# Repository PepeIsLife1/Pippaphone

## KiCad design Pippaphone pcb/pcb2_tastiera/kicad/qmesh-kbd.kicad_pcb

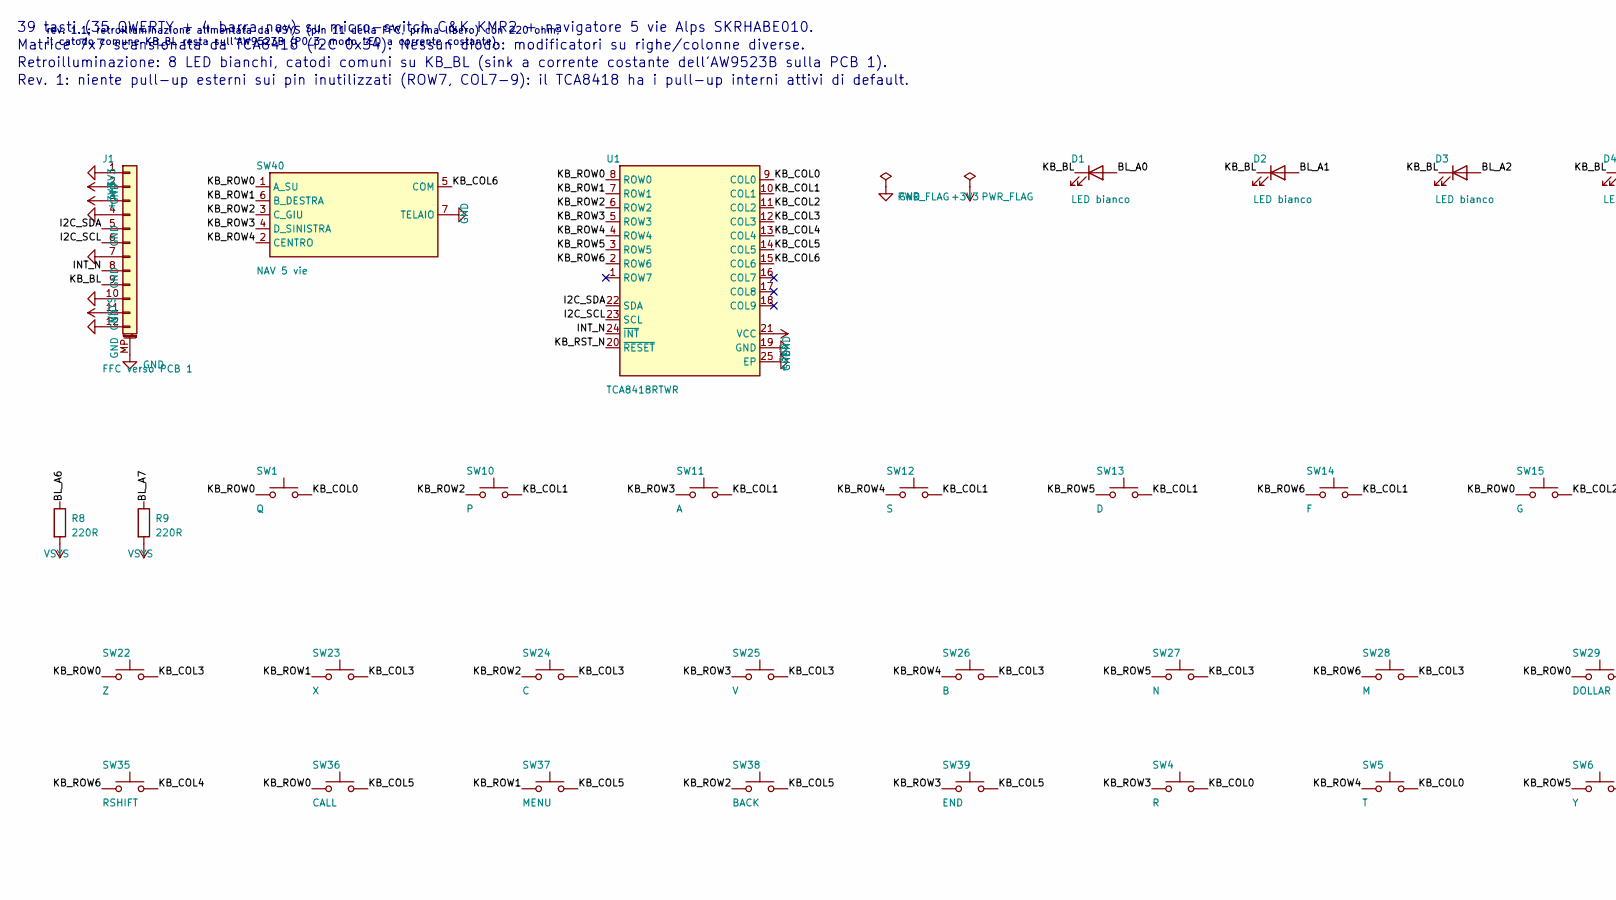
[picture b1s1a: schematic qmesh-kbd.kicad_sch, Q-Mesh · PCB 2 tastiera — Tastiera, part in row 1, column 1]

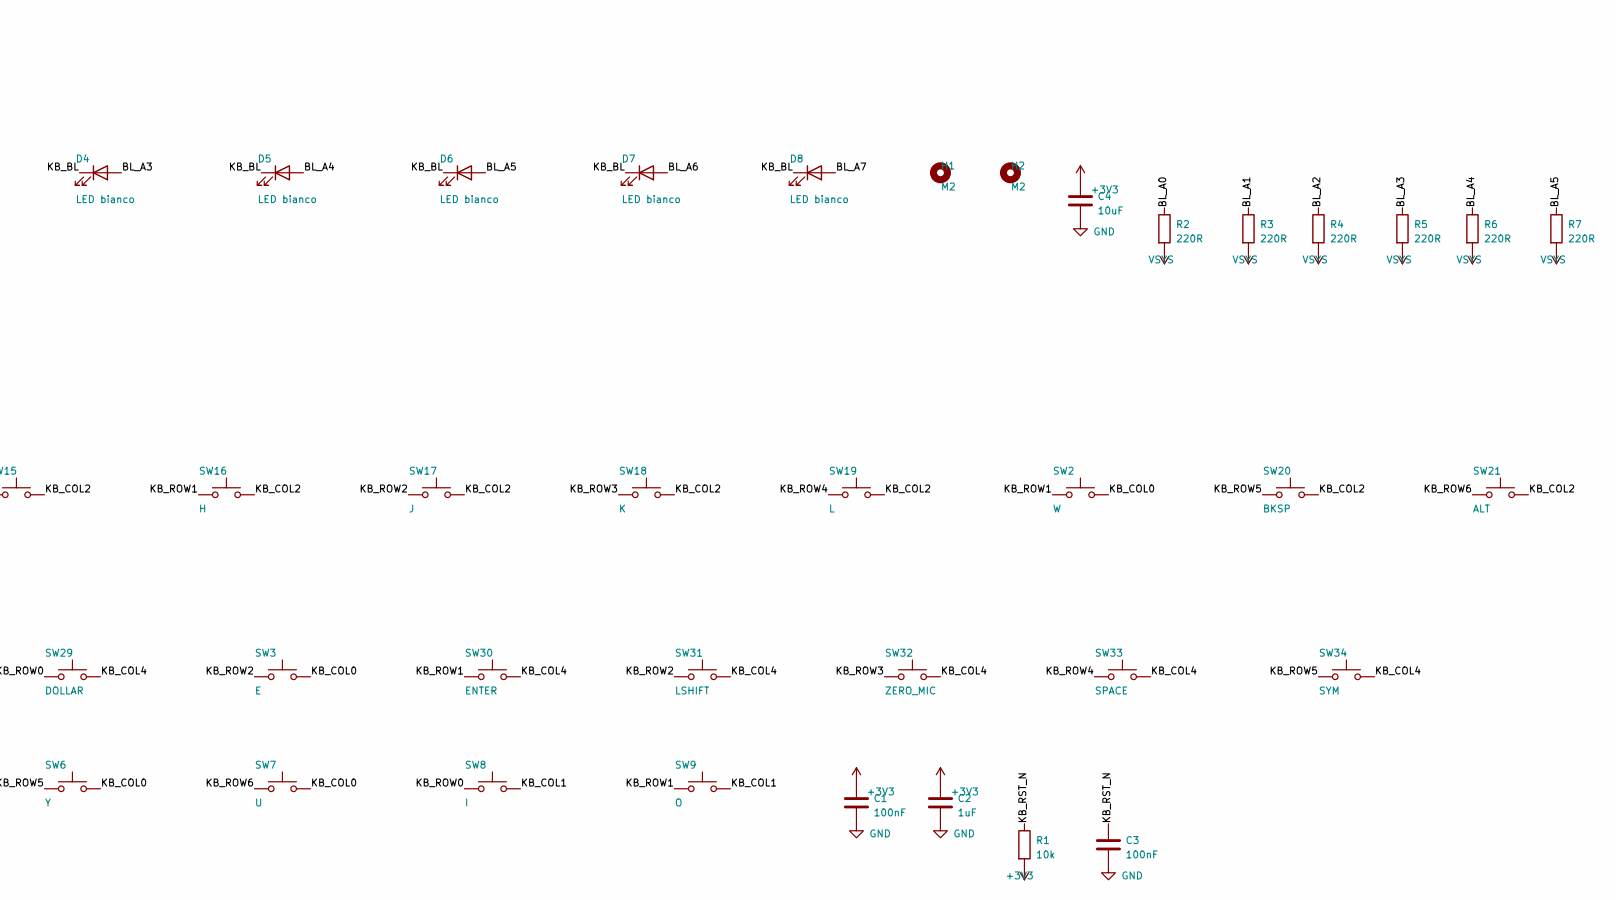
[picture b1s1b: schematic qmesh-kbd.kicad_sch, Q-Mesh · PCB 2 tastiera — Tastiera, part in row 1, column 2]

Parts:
C1, C3: 100nF; C_0402_1005Metric
C2: 1uF; C_0402_1005Metric
C4: 10uF; C_0603_1608Metric
D1, D2, D3, D4, D5, D6, D7, D8: LED bianco; LED_0603_1608Metric; MPN KT-0603W
H1, H2: M2; MountingHole_2.2mm_M2
J1: FFC verso PCB 1; Hirose_FH12-12S-0.5SH_1x12-1MP_P0.50mm_Horizontal; MPN Hirose FH12-12S-0.5SH
R1: 10k; R_0402_1005Metric
R2, R3, R4, R5, R6, R7, R8, R9: 220R; R_0402_1005Metric
SW1: Q; SW_Push_1P1T_NO_CK_KMR2; MPN C&K KMR211GLFS
SW2: W; SW_Push_1P1T_NO_CK_KMR2; MPN C&K KMR211GLFS
SW3: E; SW_Push_1P1T_NO_CK_KMR2; MPN C&K KMR211GLFS
SW4: R; SW_Push_1P1T_NO_CK_KMR2; MPN C&K KMR211GLFS
SW5: T; SW_Push_1P1T_NO_CK_KMR2; MPN C&K KMR211GLFS
SW6: Y; SW_Push_1P1T_NO_CK_KMR2; MPN C&K KMR211GLFS
SW7: U; SW_Push_1P1T_NO_CK_KMR2; MPN C&K KMR211GLFS
SW8: I; SW_Push_1P1T_NO_CK_KMR2; MPN C&K KMR211GLFS
SW9: O; SW_Push_1P1T_NO_CK_KMR2; MPN C&K KMR211GLFS
SW10: P; SW_Push_1P1T_NO_CK_KMR2; MPN C&K KMR211GLFS
SW11: A; SW_Push_1P1T_NO_CK_KMR2; MPN C&K KMR211GLFS
SW12: S; SW_Push_1P1T_NO_CK_KMR2; MPN C&K KMR211GLFS
SW13: D; SW_Push_1P1T_NO_CK_KMR2; MPN C&K KMR211GLFS
SW14: F; SW_Push_1P1T_NO_CK_KMR2; MPN C&K KMR211GLFS
SW15: G; SW_Push_1P1T_NO_CK_KMR2; MPN C&K KMR211GLFS
SW16: H; SW_Push_1P1T_NO_CK_KMR2; MPN C&K KMR211GLFS
SW17: J; SW_Push_1P1T_NO_CK_KMR2; MPN C&K KMR211GLFS
SW18: K; SW_Push_1P1T_NO_CK_KMR2; MPN C&K KMR211GLFS
SW19: L; SW_Push_1P1T_NO_CK_KMR2; MPN C&K KMR211GLFS
SW20: BKSP; SW_Push_1P1T_NO_CK_KMR2; MPN C&K KMR211GLFS
SW21: ALT; SW_Push_1P1T_NO_CK_KMR2; MPN C&K KMR211GLFS
SW22: Z; SW_Push_1P1T_NO_CK_KMR2; MPN C&K KMR211GLFS
SW23: X; SW_Push_1P1T_NO_CK_KMR2; MPN C&K KMR211GLFS
SW24: C; SW_Push_1P1T_NO_CK_KMR2; MPN C&K KMR211GLFS
SW25: V; SW_Push_1P1T_NO_CK_KMR2; MPN C&K KMR211GLFS
SW26: B; SW_Push_1P1T_NO_CK_KMR2; MPN C&K KMR211GLFS
SW27: N; SW_Push_1P1T_NO_CK_KMR2; MPN C&K KMR211GLFS
SW28: M; SW_Push_1P1T_NO_CK_KMR2; MPN C&K KMR211GLFS
SW29: DOLLAR; SW_Push_1P1T_NO_CK_KMR2; MPN C&K KMR211GLFS
SW30: ENTER; SW_Push_1P1T_NO_CK_KMR2; MPN C&K KMR211GLFS
SW31: LSHIFT; SW_Push_1P1T_NO_CK_KMR2; MPN C&K KMR211GLFS
SW32: ZERO_MIC; SW_Push_1P1T_NO_CK_KMR2; MPN C&K KMR211GLFS
SW33: SPACE; SW_Push_1P1T_NO_CK_KMR2; MPN C&K KMR211GLFS
SW34: SYM; SW_Push_1P1T_NO_CK_KMR2; MPN C&K KMR211GLFS
SW35: RSHIFT; SW_Push_1P1T_NO_CK_KMR2; MPN C&K KMR211GLFS
SW36: CALL; SW_Push_1P1T_NO_CK_KMR2; MPN C&K KMR211GLFS
SW37: MENU; SW_Push_1P1T_NO_CK_KMR2; MPN C&K KMR211GLFS
SW38: BACK; SW_Push_1P1T_NO_CK_KMR2; MPN C&K KMR211GLFS
SW39: END; SW_Push_1P1T_NO_CK_KMR2; MPN C&K KMR211GLFS
SW40: NAV 5 vie; Alps_SKRHA_5way; MPN Alps SKRHABE010
U1: TCA8418RTWR; QFN-24-1EP_4x4mm_P0.5mm_EP2.6x2.6mm; MPN TCA8418RTWR

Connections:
+3V3: C1.1, C2.1, C4.1, J1.2, J1.3, R1.2, U1.21 (VCC)
BL_A0: D1.2 (A), R2.1
BL_A1: D2.2 (A), R3.1
BL_A2: D3.2 (A), R4.1
BL_A3: D4.2 (A), R5.1
BL_A4: D5.2 (A), R6.1
BL_A5: D6.2 (A), R7.1
BL_A6: D7.2 (A), R8.1
BL_A7: D8.2 (A), R9.1
GND: C1.2, C2.2, C3.2, C4.2, J1.1, J1.4, J1.7, J1.10, J1.12, J1.MP (MountPin), SW40.7 (TELAIO), U1.19 (GND), U1.25 (EP)
I2C_SCL: J1.6, U1.23 (SCL)
I2C_SDA: J1.5, U1.22 (SDA)
INT_N: J1.8, U1.24 (~INT)
KB_BL: D1.1 (K), D2.1 (K), D3.1 (K), D4.1 (K), D5.1 (K), D6.1 (K), D7.1 (K), D8.1 (K), J1.9
KB_COL0: SW1.2, SW2.2, SW3.2, SW4.2, SW5.2, SW6.2, SW7.2, U1.9 (COL0)
KB_COL1: SW8.2, SW9.2, SW10.2, SW11.2, SW12.2, SW13.2, SW14.2, U1.10 (COL1)
KB_COL2: SW15.2, SW16.2, SW17.2, SW18.2, SW19.2, SW20.2, SW21.2, U1.11 (COL2)
KB_COL3: SW22.2, SW23.2, SW24.2, SW25.2, SW26.2, SW27.2, SW28.2, U1.12 (COL3)
KB_COL4: SW29.2, SW30.2, SW31.2, SW32.2, SW33.2, SW34.2, SW35.2, U1.13 (COL4)
KB_COL5: SW36.2, SW37.2, SW38.2, SW39.2, U1.14 (COL5)
KB_COL6: SW40.5 (COM), U1.15 (COL6)
KB_ROW0: SW1.1, SW8.1, SW15.1, SW22.1, SW29.1, SW36.1, SW40.1 (A_SU), U1.8 (ROW0)
KB_ROW1: SW2.1, SW9.1, SW16.1, SW23.1, SW30.1, SW37.1, SW40.6 (B_DESTRA), U1.7 (ROW1)
KB_ROW2: SW3.1, SW10.1, SW17.1, SW24.1, SW31.1, SW38.1, SW40.3 (C_GIU), U1.6 (ROW2)
KB_ROW3: SW4.1, SW11.1, SW18.1, SW25.1, SW32.1, SW39.1, SW40.4 (D_SINISTRA), U1.5 (ROW3)
KB_ROW4: SW5.1, SW12.1, SW19.1, SW26.1, SW33.1, SW40.2 (CENTRO), U1.4 (ROW4)
KB_ROW5: SW6.1, SW13.1, SW20.1, SW27.1, SW34.1, U1.3 (ROW5)
KB_ROW6: SW7.1, SW14.1, SW21.1, SW28.1, SW35.1, U1.2 (ROW6)
KB_RST_N: C3.1, R1.1, U1.20 (~RESET)
VSYS: J1.11, R2.2, R3.2, R4.2, R5.2, R6.2, R7.2, R8.2, R9.2

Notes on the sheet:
39 tasti (35 QWERTY + 4 barra nav) su micro-switch C&K KMR2 + navigatore 5 vie Alps SKRHABE010.
Matrice 7x7 scansionata da TCA8418 (I2C 0x34). Nessun diodo: modificatori su righe/colonne diverse.
Retroilluminazione: 8 LED bianchi, catodi comuni su KB_BL (sink a corrente costante dell'AW9523B sulla PCB 1).
Rev. 1: niente pull-up esterni sui pin inutilizzati (ROW7, COL7-9): il TCA8418 ha i pull-up interni attivi di default.
rev. 1.1: retroilluminazione alimentata da VSYS (pin 11 della FFC, prima libero) con 220 ohm; il catodo comune KB_BL resta sull'AW9523B (P0_3, modo LED a corrente costante).

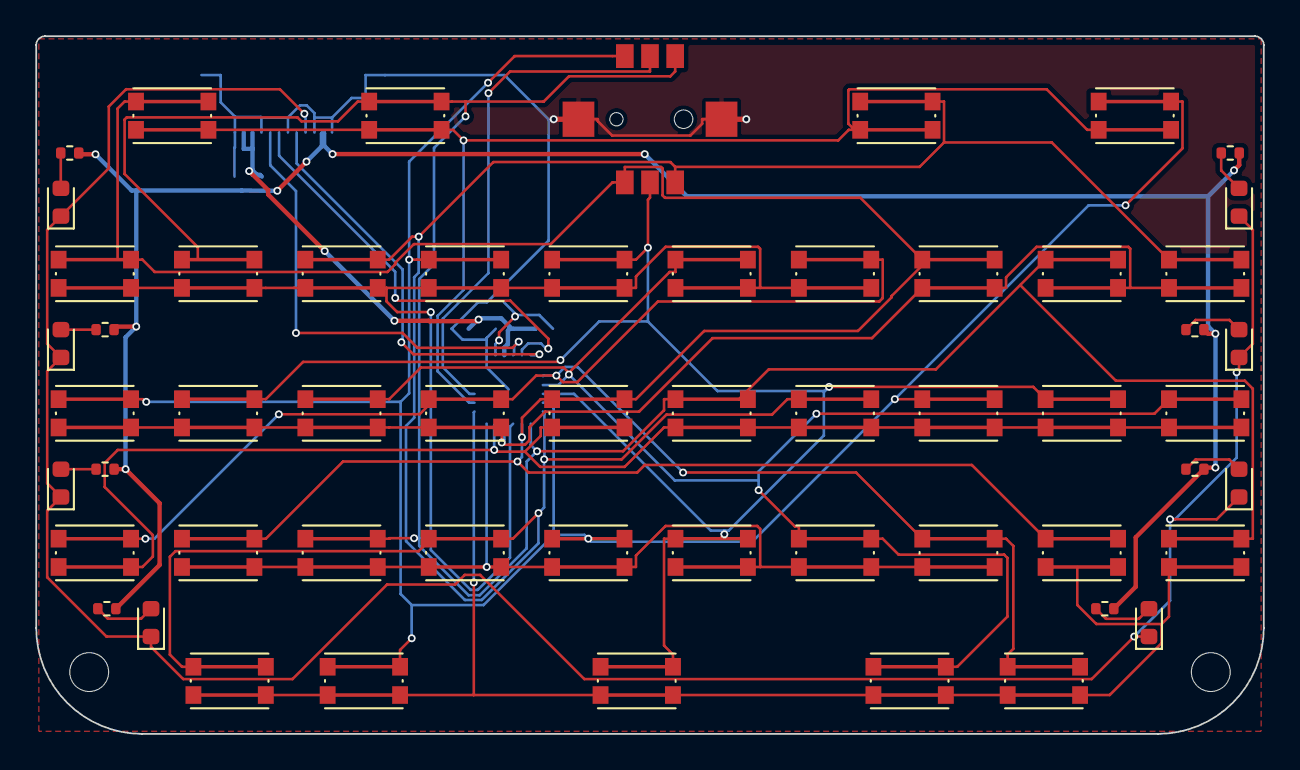
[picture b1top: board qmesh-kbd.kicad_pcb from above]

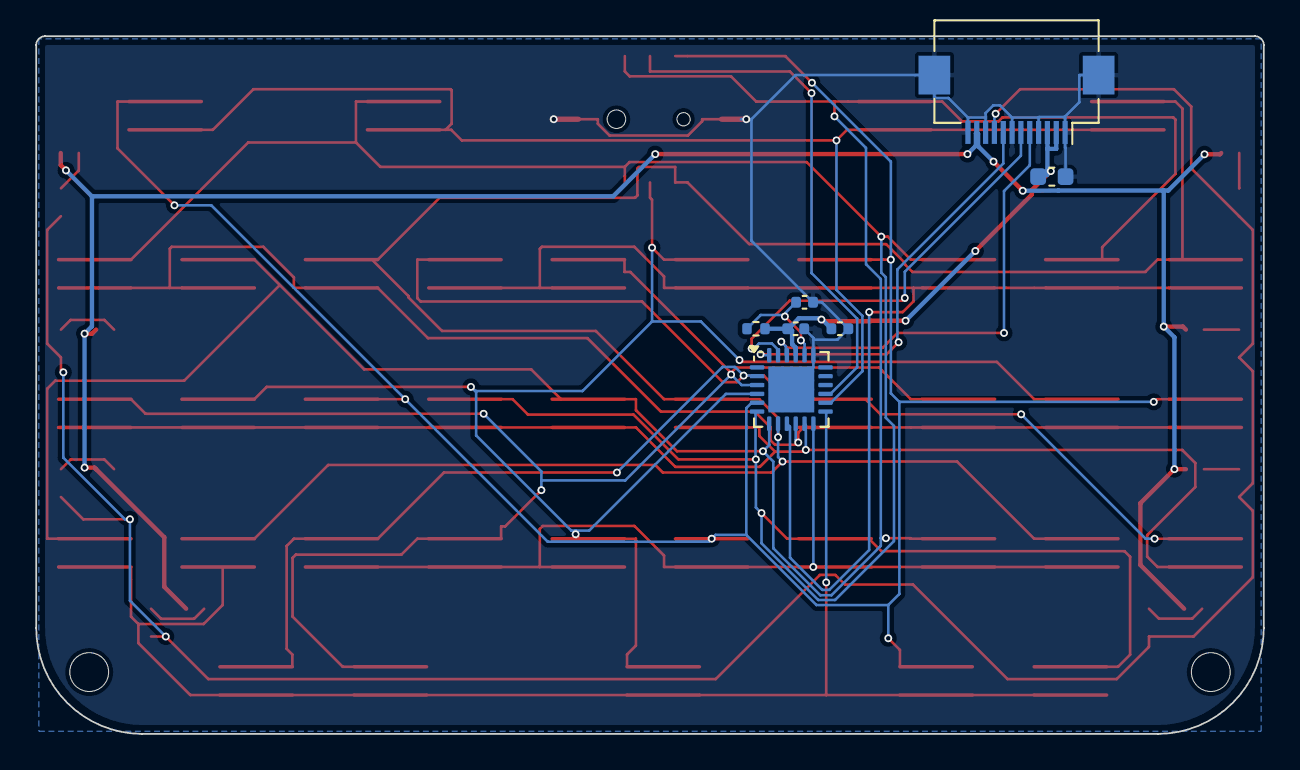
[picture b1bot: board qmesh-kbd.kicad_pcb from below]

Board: 2 copper layers, 69.5 x 39.5 mm, 65 parts (7 on the bottom side), 30 nets.

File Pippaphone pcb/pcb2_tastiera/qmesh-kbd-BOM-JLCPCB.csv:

Comment,Designator,Footprint,MPN,LCSC Part #,Quantity,Note
100nF,"C1,C3",C_0402_1005Metric,CL05B104KO5NNNC,C1525,2,
1uF,C2,C_0402_1005Metric,CL05A105KA5NQNC,C52923,1,
10uF,C4,C_0603_1608Metric,CL10A106KP8NNNC,C19702,1,
LED bianco,"D1,D2,D3,D4,D5,D6,D7,D8",LED_0603_1608Metric,KT-0603W,C2290,8,
FFC verso PCB 1,J1,Hirose_FH12-12S-0.5SH_1x12-1MP_P0.50mm_Horizontal,Hirose FH12-12S-0.5SH(55),C88360,1,
10k,R1,R_0402_1005Metric,0402WGF1002TCE,C25744,1,
KMR211GLFS,"SW1,SW2,SW3,SW4,SW5,SW6,SW7,SW8,SW9,SW10,SW11,SW12,SW13,SW14,SW15,SW16,SW17,SW18,SW19,SW20,SW21,SW22,SW23,SW24,SW25,SW26,SW27,SW28,SW29,SW30,SW31,SW32,SW33,SW34,SW35,SW36,SW37,SW38,SW39",SW_Push_1P1T_NO_CK_KMR2,C&K KMR211GLFS,C221675,39,
NAV 5 vie,SW40,Alps_SKRHA_5way,Alps SKRHABE010,C139794,1,
TCA8418RTWR,U1,QFN-24-1EP_4x4mm_P0.5mm_EP2.6x2.6mm,TCA8418RTWR,C138713,1,
220R,"R2,R3,R4,R5,R6,R7,R8,R9",R_0402_1005Metric,0402WGF2200TCE,C25091,8,

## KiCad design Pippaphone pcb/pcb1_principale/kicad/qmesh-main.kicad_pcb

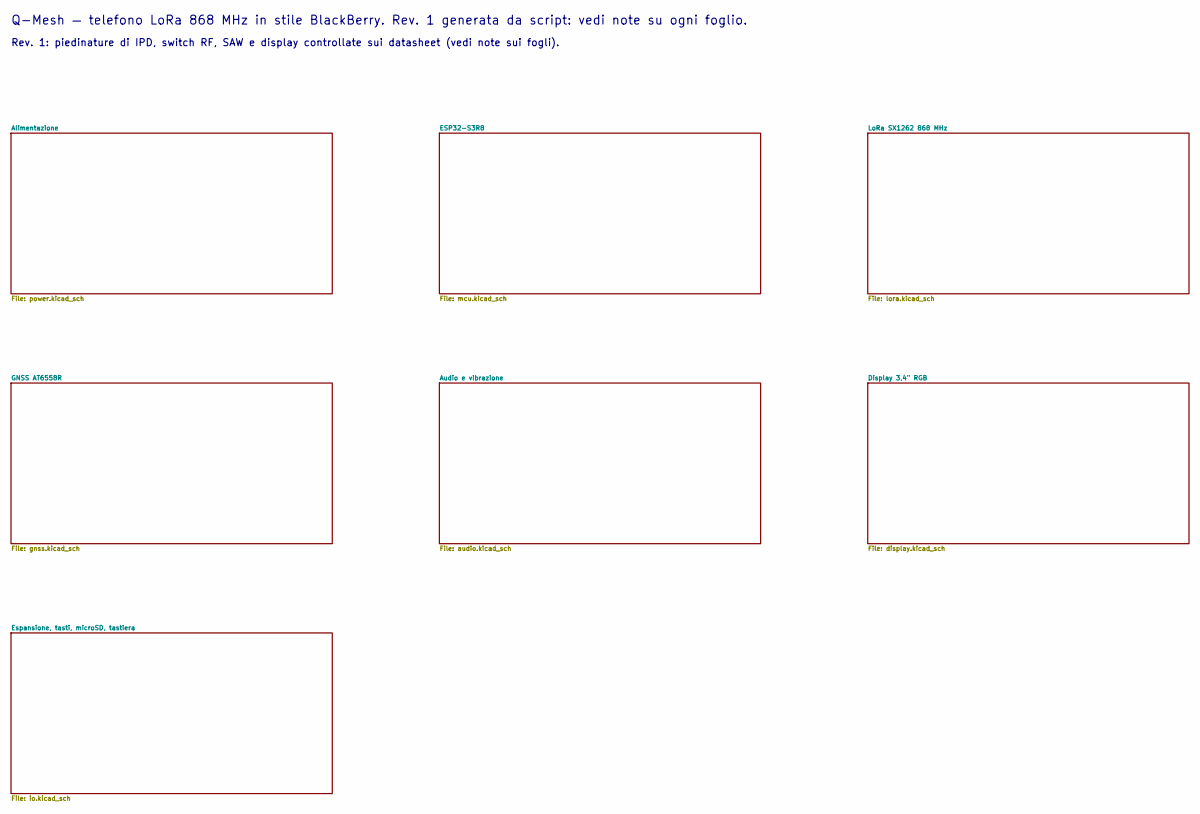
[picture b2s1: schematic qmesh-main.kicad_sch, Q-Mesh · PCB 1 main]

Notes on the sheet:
Q-Mesh — telefono LoRa 868 MHz in stile BlackBerry. Rev. 1 generata da script: vedi note su ogni foglio.
Rev. 1: piedinature di IPD, switch RF, SAW e display controllate sui datasheet (vedi note sui fogli).

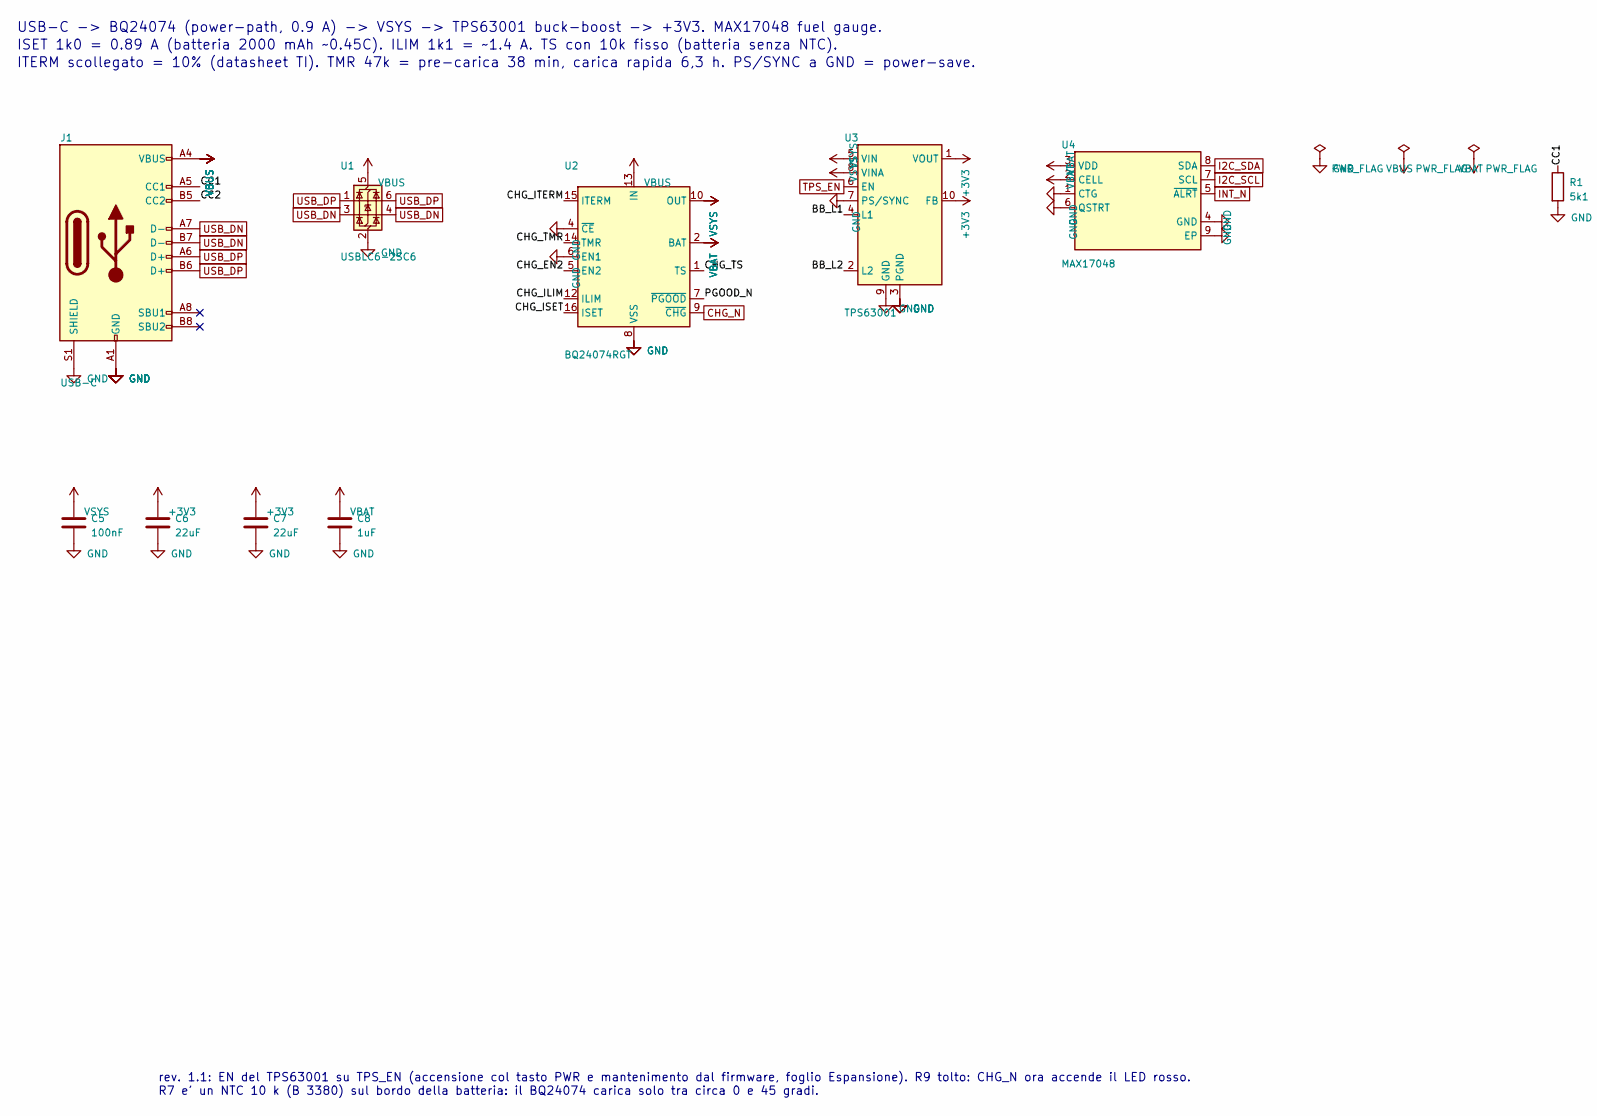
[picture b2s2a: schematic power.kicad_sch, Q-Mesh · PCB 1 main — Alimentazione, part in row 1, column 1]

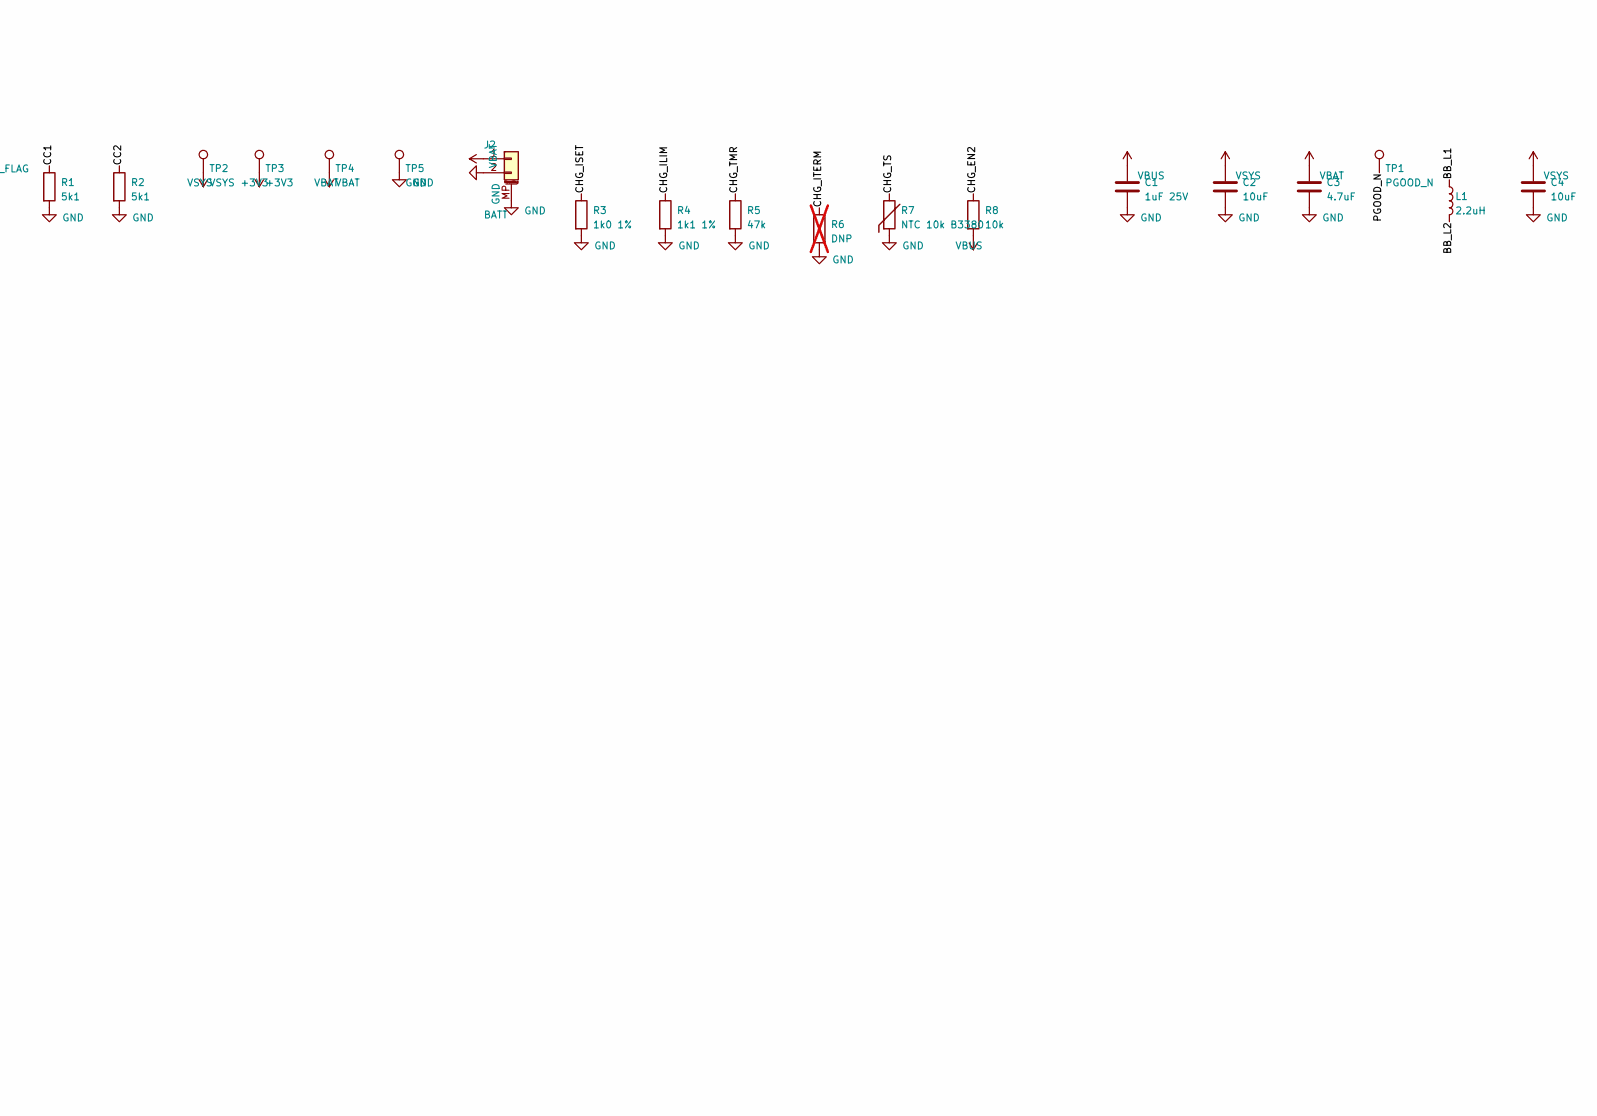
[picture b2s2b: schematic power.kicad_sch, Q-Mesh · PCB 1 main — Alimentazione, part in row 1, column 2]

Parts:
C1: 1uF 25V; C_0603_1608Metric
C2, C4: 10uF; C_0603_1608Metric
C3: 4.7uF; C_0603_1608Metric
C5: 100nF; C_0402_1005Metric
C6, C7: 22uF; C_0805_2012Metric
C8: 1uF; C_0402_1005Metric
J1: USB-C; USB_C_Receptacle_HRO_TYPE-C-31-M-12; MPN HRO TYPE-C-31-M-12
J2: BATT; JST_SH_SM02B-SRSS-TB_1x02-1MP_P1.00mm_Horizontal; MPN JST SM02B-SRSS-TB
L1: 2.2uH; L_Changjiang_FNR252012S; MPN FTC252012S2R2MBCA
R1, R2: 5k1; R_0402_1005Metric
R3: 1k0 1%; R_0402_1005Metric
R4: 1k1 1%; R_0402_1005Metric
R5: 47k; R_0402_1005Metric
R6: DNP; R_0402_1005Metric; not fitted
R7: NTC 10k B3380; R_0402_1005Metric; MPN NCP15XH103F03RC
R8: 10k; R_0402_1005Metric
TP1: PGOOD_N; TestPoint_Pad_D1.0mm
TP2: VSYS; TestPoint_Pad_D1.0mm
TP3: +3V3; TestPoint_Pad_D1.0mm
TP4: VBAT; TestPoint_Pad_D1.0mm
TP5: GND; TestPoint_Pad_D1.0mm
U1: USBLC6-2SC6; SOT-23-6; MPN USBLC6-2SC6
U2: BQ24074RGT; VQFN-16-1EP_3x3mm_P0.5mm_EP1.6x1.6mm; MPN BQ24074RGTR
U3: TPS63001; Texas_DRC0010J_ThermalVias; MPN TPS63001DRCR
U4: MAX17048; TDFN-8-1EP_2x2mm_P0.5mm_EP0.8x1.2mm; MPN MAX17048G+T10

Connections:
+3V3: C6.1, C7.1, TP3.1, U3.1 (VOUT), U3.10 (FB); also elsewhere on the board
BB_L1: L1.1, U3.4 (L1)
BB_L2: L1.2, U3.2 (L2)
CC1: J1.A5 (CC1), R1.1
CC2: J1.B5 (CC2), R2.1
CHG_EN2: R8.1, U2.5 (EN2)
CHG_ILIM: R4.1, U2.12 (ILIM)
CHG_ISET: R3.1, U2.16 (ISET)
CHG_ITERM: R6.1, U2.15 (ITERM)
CHG_N: U2.9 (~CHG); also elsewhere on the board
CHG_TMR: R5.1, U2.14 (TMR)
CHG_TS: R7.1, U2.1 (TS)
GND: C1.2, C2.2, C3.2, C4.2, C5.2, C6.2, C7.2, C8.2, J1.A1 (GND), J1.A12 (GND), J1.B1 (GND), J1.B12 (GND), J1.S1 (SHIELD), J2.2, J2.MP (MountPin), R1.2, R2.2, R3.2, R4.2, R5.2, R6.2, R7.2, TP5.1, U1.2 (GND), U2.4 (~CE), U2.6 (EN1), U2.8 (VSS), U2.17 (VSS), U3.3 (PGND), U3.7 (PS/SYNC), U3.9 (GND), U3.11 (PGND), U4.1 (CTG), U4.4 (GND), U4.6 (QSTRT), U4.9 (EP); also elsewhere on the board
I2C_SCL: U4.7 (SCL); also elsewhere on the board
I2C_SDA: U4.8 (SDA); also elsewhere on the board
INT_N: U4.5 (~ALRT); also elsewhere on the board
PGOOD_N: TP1.1, U2.7 (~PGOOD)
TPS_EN: U3.6 (EN); also elsewhere on the board
USB_DN: J1.A7 (D-), J1.B7 (D-), U1.3 (I/O2), U1.4 (I/O2); also elsewhere on the board
USB_DP: J1.A6 (D+), J1.B6 (D+), U1.1 (I/O1), U1.6 (I/O1); also elsewhere on the board
VBAT: C3.1, C8.1, J2.1, TP4.1, U2.2 (BAT), U2.3 (BAT), U4.2 (CELL), U4.3 (VDD)
VBUS: C1.1, J1.A4 (VBUS), J1.A9 (VBUS), J1.B4 (VBUS), J1.B9 (VBUS), R8.2, U1.5 (VBUS), U2.13 (IN)
VSYS: C2.1, C4.1, C5.1, TP2.1, U2.10 (OUT), U2.11 (OUT), U3.5 (VIN), U3.8 (VINA); also elsewhere on the board

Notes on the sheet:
USB-C -> BQ24074 (power-path, 0.9 A) -> VSYS -> TPS63001 buck-boost -> +3V3. MAX17048 fuel gauge.
ISET 1k0 = 0.89 A (batteria 2000 mAh ~0.45C). ILIM 1k1 = ~1.4 A. TS con 10k fisso (batteria senza NTC).
ITERM scollegato = 10% (datasheet TI). TMR 47k = pre-carica 38 min, carica rapida 6,3 h. PS/SYNC a GND = power-save.
rev. 1.1: EN del TPS63001 su TPS_EN (accensione col tasto PWR e mantenimento dal firmware, foglio Espansione). R9 tolto: CHG_N ora accende il LED rosso. R7 e' un NTC 10 k (B 3380) sul bordo della batteria: il BQ24074 carica solo tra circa 0 e 45 gradi.

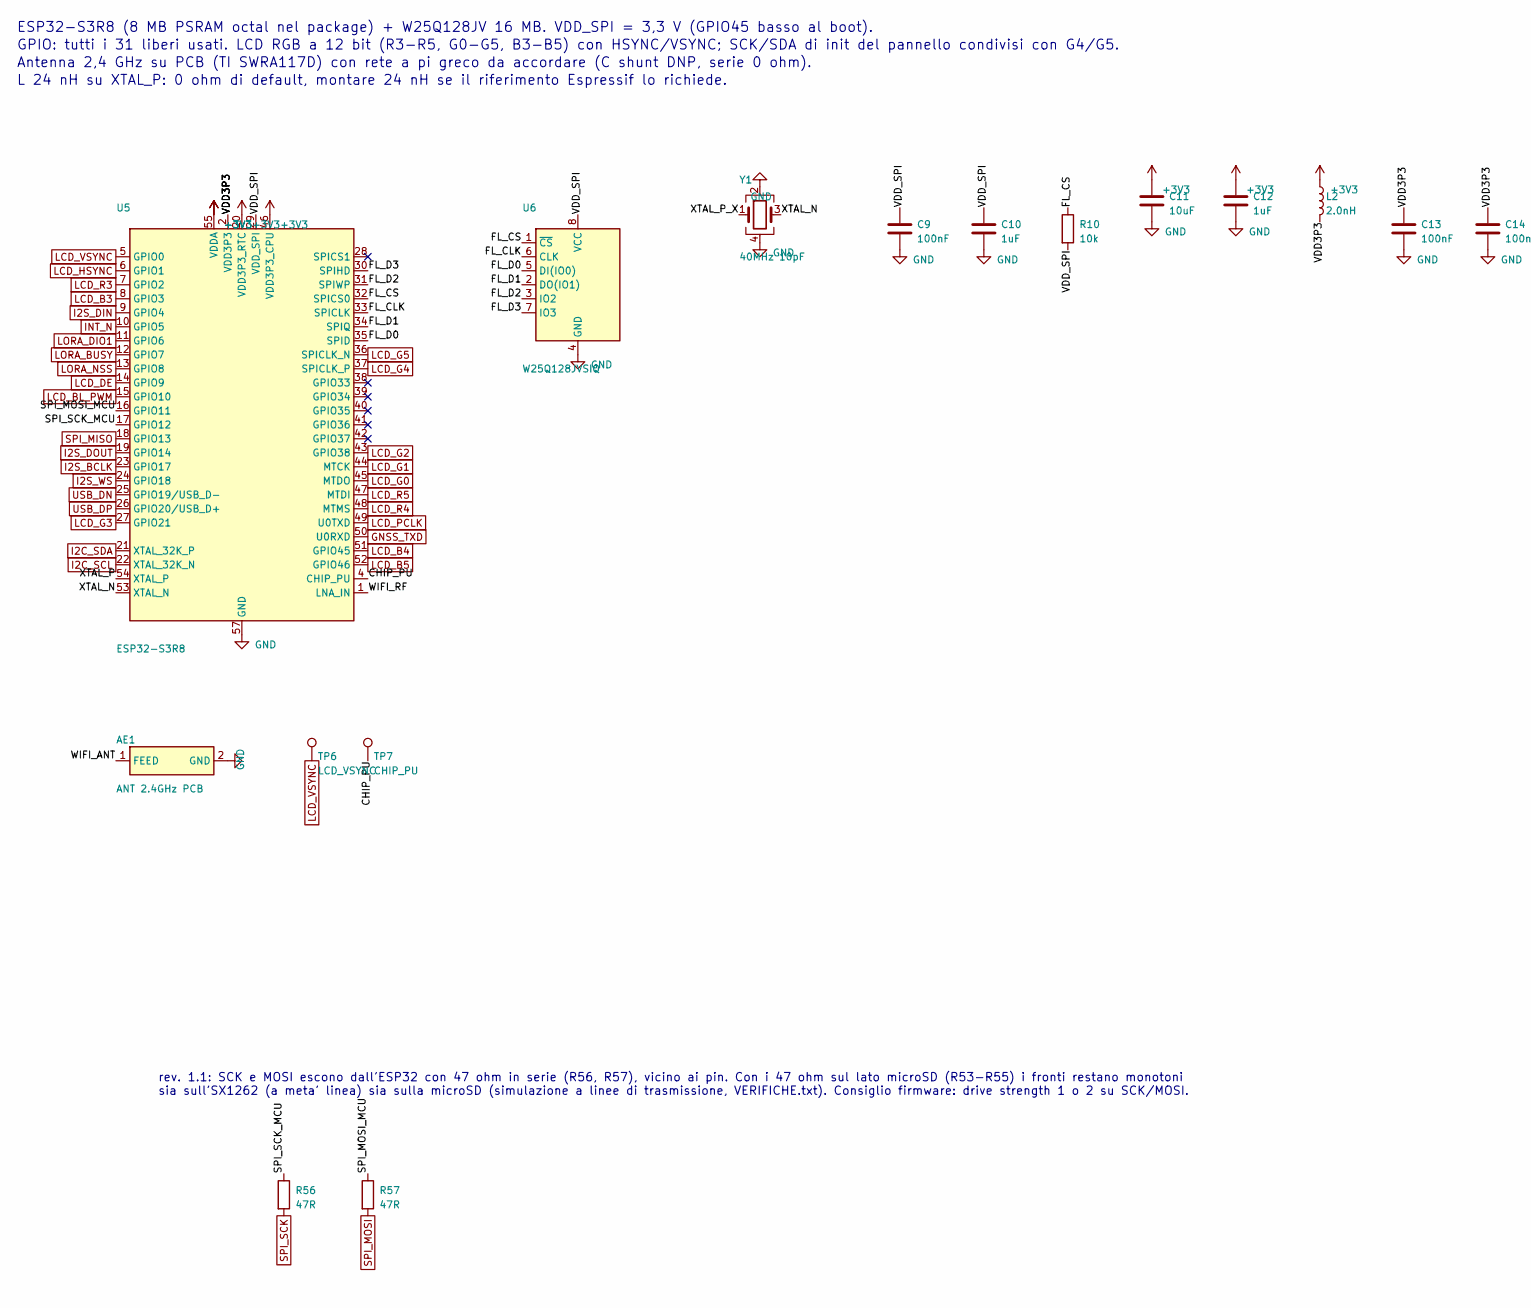
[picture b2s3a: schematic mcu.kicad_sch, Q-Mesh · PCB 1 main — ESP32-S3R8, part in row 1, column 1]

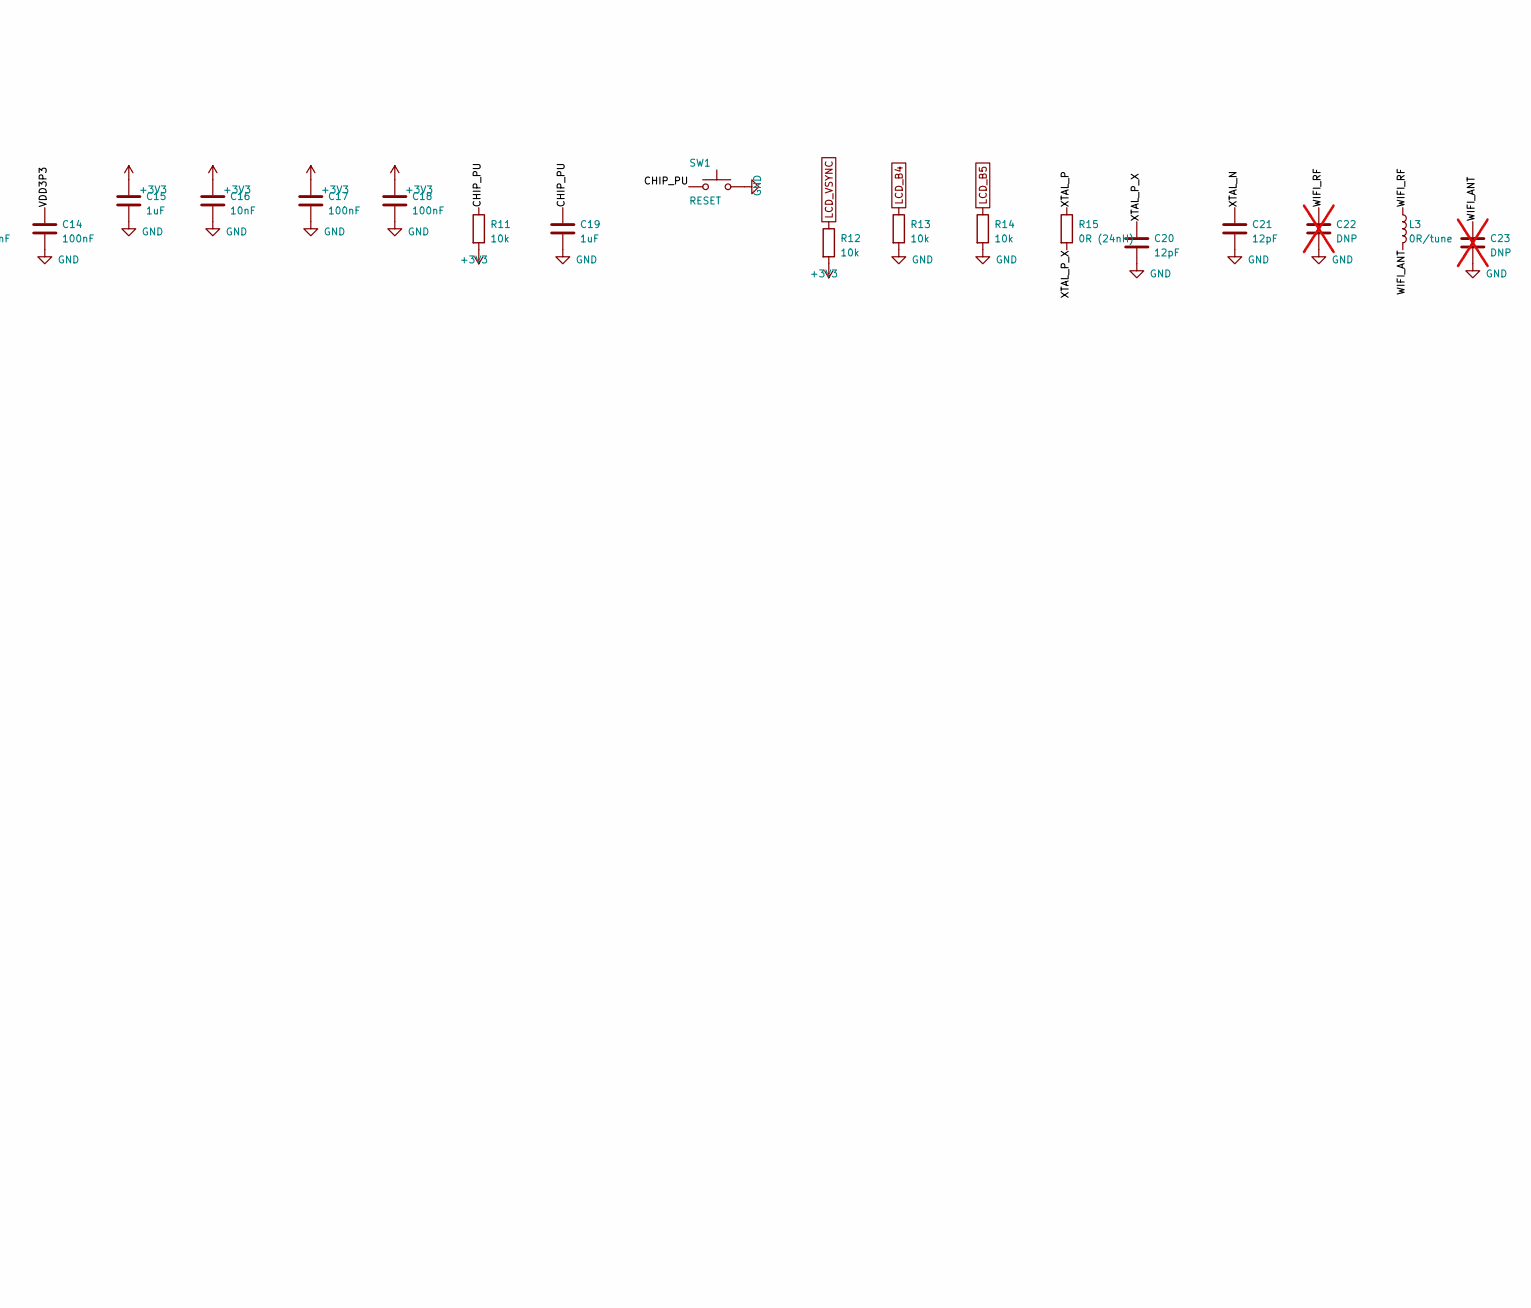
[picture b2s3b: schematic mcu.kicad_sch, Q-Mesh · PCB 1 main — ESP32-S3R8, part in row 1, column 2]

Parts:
AE1: ANT 2.4GHz PCB; Texas_SWRA117D_2.4GHz_Left
C9, C13, C14, C17, C18: 100nF; C_0402_1005Metric
C10, C12, C15, C19: 1uF; C_0402_1005Metric
C11: 10uF; C_0603_1608Metric
C16: 10nF; C_0402_1005Metric
C20, C21: 12pF; C_0402_1005Metric
C22, C23: DNP; C_0402_1005Metric; not fitted
L2: 2.0nH; L_0402_1005Metric; MPN LQG15HS2N0
L3: 0R/tune; L_0402_1005Metric
R10, R11, R12, R13, R14: 10k; R_0402_1005Metric
R15: 0R (24nH); R_0402_1005Metric
R56, R57: 47R; R_0402_1005Metric; MPN 0402WGF470JTCE
SW1: RESET; SW_Push_1P1T_NO_CK_KMR2; MPN KMR221GLFS
TP6: LCD_VSYNC; TestPoint_Pad_D1.0mm
TP7: CHIP_PU; TestPoint_Pad_D1.0mm
U5: ESP32-S3R8; QFN-56-1EP_7x7mm_P0.4mm_EP4x4mm; MPN ESP32-S3R8
U6: W25Q128JVSIQ; SOIC-8_5.23x5.23mm_P1.27mm; MPN W25Q128JVSIQ
Y1: 40MHz 10pF; Crystal_SMD_3225-4Pin_3.2x2.5mm; MPN SX3B40.000F1010F30

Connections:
+3V3: C11.1, C12.1, C15.1, C16.1, C17.1, C18.1, L2.1, R11.2, R12.2, U5.20 (VDD3P3_RTC), U5.46 (VDD3P3_CPU), U5.55 (VDDA), U5.56 (VDDA); also elsewhere on the board
CHIP_PU: C19.1, R11.1, SW1.1, TP7.1, U5.4 (CHIP_PU)
FL_CLK: U5.33 (SPICLK), U6.6 (CLK)
FL_CS: R10.1, U5.32 (SPICS0), U6.1 (~CS)
FL_D0: U5.35 (SPID), U6.5 (DI(IO0))
FL_D1: U5.34 (SPIQ), U6.2 (DO(IO1))
FL_D2: U5.31 (SPIWP), U6.3 (IO2)
FL_D3: U5.30 (SPIHD), U6.7 (IO3)
GND: AE1.2 (GND), C9.2, C10.2, C11.2, C12.2, C13.2, C14.2, C15.2, C16.2, C17.2, C18.2, C19.2, C20.2, C21.2, C22.2, C23.2, R13.2, R14.2, SW1.2, U5.57 (GND), U6.4 (GND), Y1.2, Y1.4; also elsewhere on the board
GNSS_TXD: U5.50 (U0RXD); also elsewhere on the board
I2C_SCL: U5.22 (XTAL_32K_N); also elsewhere on the board
I2C_SDA: U5.21 (XTAL_32K_P); also elsewhere on the board
I2S_BCLK: U5.23 (GPIO17); also elsewhere on the board
I2S_DIN: U5.9 (GPIO4); also elsewhere on the board
I2S_DOUT: U5.19 (GPIO14); also elsewhere on the board
I2S_WS: U5.24 (GPIO18); also elsewhere on the board
INT_N: U5.10 (GPIO5); also elsewhere on the board
LCD_B3: U5.8 (GPIO3); also elsewhere on the board
LCD_B4: R13.1, U5.51 (GPIO45); also elsewhere on the board
LCD_B5: R14.1, U5.52 (GPIO46); also elsewhere on the board
LCD_BL_PWM: U5.15 (GPIO10); also elsewhere on the board
LCD_DE: U5.14 (GPIO9); also elsewhere on the board
LCD_G0: U5.45 (MTDO); also elsewhere on the board
LCD_G1: U5.44 (MTCK); also elsewhere on the board
LCD_G2: U5.43 (GPIO38); also elsewhere on the board
LCD_G3: U5.27 (GPIO21); also elsewhere on the board
LCD_G4: U5.37 (SPICLK_P); also elsewhere on the board
LCD_G5: U5.36 (SPICLK_N); also elsewhere on the board
LCD_HSYNC: U5.6 (GPIO1); also elsewhere on the board
LCD_PCLK: U5.49 (U0TXD); also elsewhere on the board
LCD_R3: U5.7 (GPIO2); also elsewhere on the board
LCD_R4: U5.48 (MTMS); also elsewhere on the board
LCD_R5: U5.47 (MTDI); also elsewhere on the board
LCD_VSYNC: R12.1, TP6.1, U5.5 (GPIO0); also elsewhere on the board
LORA_BUSY: U5.12 (GPIO7); also elsewhere on the board
LORA_DIO1: U5.11 (GPIO6); also elsewhere on the board
LORA_NSS: U5.13 (GPIO8); also elsewhere on the board
SPI_MISO: U5.18 (GPIO13); also elsewhere on the board
SPI_MOSI: R57.2; also elsewhere on the board
SPI_MOSI_MCU: R57.1, U5.16 (GPIO11)
SPI_SCK: R56.2; also elsewhere on the board
SPI_SCK_MCU: R56.1, U5.17 (GPIO12)
USB_DN: U5.25 (GPIO19/USB_D-); also elsewhere on the board
USB_DP: U5.26 (GPIO20/USB_D+); also elsewhere on the board
VDD3P3: C13.1, C14.1, L2.2, U5.2 (VDD3P3), U5.3 (VDD3P3)
VDD_SPI: C9.1, C10.1, R10.2, U5.29 (VDD_SPI), U6.8 (VCC)
WIFI_ANT: AE1.1 (FEED), C23.1, L3.2
WIFI_RF: C22.1, L3.1, U5.1 (LNA_IN)
XTAL_N: C21.1, U5.53 (XTAL_N), Y1.3
XTAL_P: R15.1, U5.54 (XTAL_P)
XTAL_P_X: C20.1, R15.2, Y1.1

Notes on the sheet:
ESP32-S3R8 (8 MB PSRAM octal nel package) + W25Q128JV 16 MB. VDD_SPI = 3,3 V (GPIO45 basso al boot).
GPIO: tutti i 31 liberi usati. LCD RGB a 12 bit (R3-R5, G0-G5, B3-B5) con HSYNC/VSYNC; SCK/SDA di init del pannello condivisi con G4/G5.
Antenna 2,4 GHz su PCB (TI SWRA117D) con rete a pi greco da accordare (C shunt DNP, serie 0 ohm).
L 24 nH su XTAL_P: 0 ohm di default, montare 24 nH se il riferimento Espressif lo richiede.
rev. 1.1: SCK e MOSI escono dall'ESP32 con 47 ohm in serie (R56, R57), vicino ai pin. Con i 47 ohm sul lato microSD (R53-R55) i fronti restano monotoni sia sull'SX1262 (a meta' linea) sia sulla microSD (simulazione a linee di trasmissione, VERIFICHE.txt). Consiglio firmware: drive strength 1 o 2 su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
